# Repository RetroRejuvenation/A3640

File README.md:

# a3640
Somewhere for the A3640 project to live

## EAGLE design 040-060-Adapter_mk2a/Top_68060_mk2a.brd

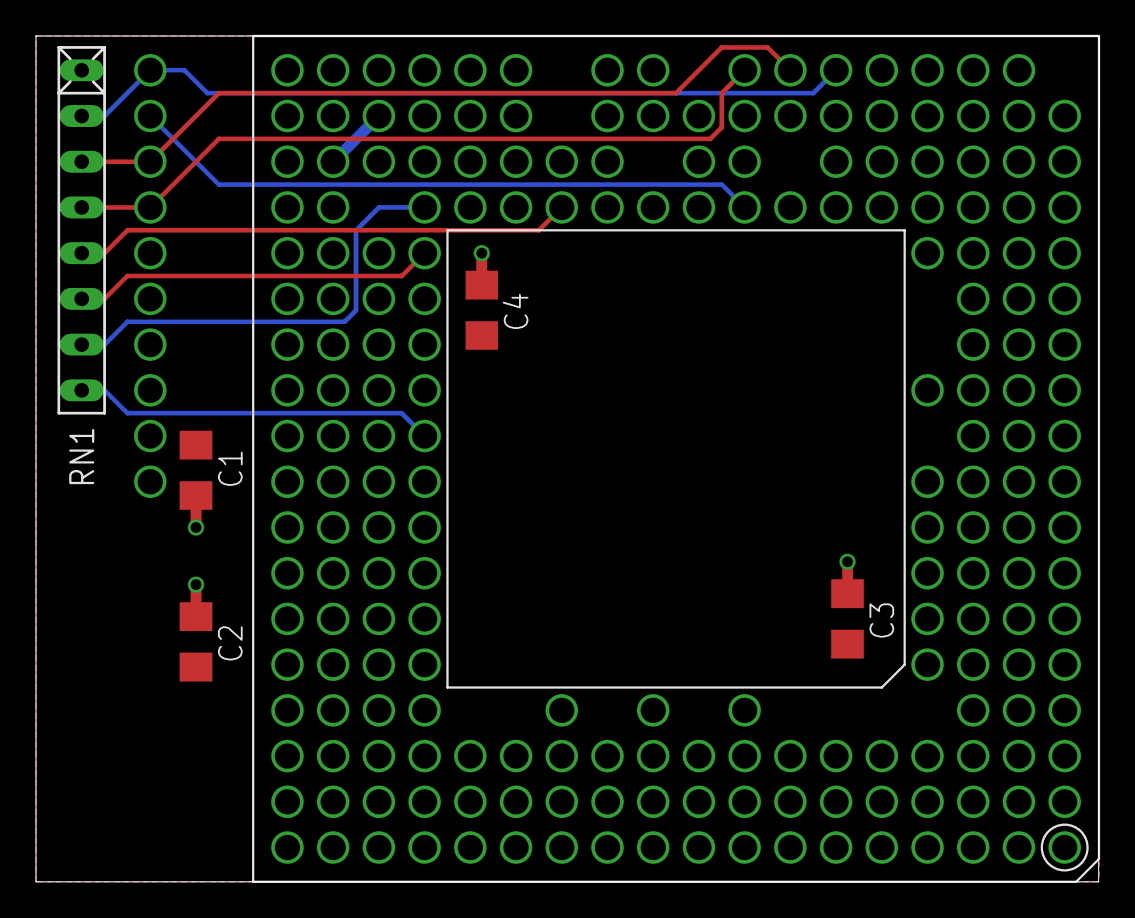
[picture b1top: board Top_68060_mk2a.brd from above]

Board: 2 copper layers, 59.1 x 47.0 mm, 7 parts (0 on the bottom side), 10 nets.

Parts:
C1, C2, C3, C4: 100n; C1206
IC1: MC68060RCPGA_BIG; PGA206_BIG
RN1: 4k7; RN-8
U$1: 10POL; 10-PIN-1.4HOLES

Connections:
+3V3: C1.1, C2.1, C3.1, C4.1, IC1.B05, IC1.B09, IC1.B14, IC1.C02, IC1.C05, IC1.C08, IC1.C10, IC1.C12, IC1.C14, IC1.C17, IC1.D08, IC1.D10, IC1.D12, IC1.D15, IC1.E04, IC1.E15, IC1.G02, IC1.G04, IC1.G15, IC1.G17, IC1.H03, IC1.H16, IC1.J03, IC1.J04, IC1.J15, IC1.J16, IC1.L04, IC1.L16, IC1.M02, IC1.M03, IC1.M17, IC1.N15, IC1.P04, IC1.Q10, IC1.R02, IC1.R05, IC1.R08, IC1.R12, IC1.R17, IC1.S08, IC1.S16, RN1.1, U$1.P$5, U$1.P$6, U$1.P$7, U$1.P$8, U$1.P$9, U$1.P$10
BTT: IC1.Q15, RN1.7
CLA: IC1.K15, RN1.8
CLKEN: IC1.Q08, U$1.P$2
GND: C1.2, C2.2, C3.2, C4.2, IC1.B02, IC1.B04, IC1.B06, IC1.B08, IC1.B10, IC1.B13, IC1.B15, IC1.B17, IC1.C06, IC1.C07, IC1.C09, IC1.C11, IC1.C13, IC1.D02, IC1.D17, IC1.F02, IC1.F04, IC1.F15, IC1.F17, IC1.H02, IC1.H04, IC1.H15, IC1.H17, IC1.K03, IC1.K16, IC1.L02, IC1.L03, IC1.L17, IC1.M16, IC1.N02, IC1.N17, IC1.Q02, IC1.Q09, IC1.Q11, IC1.Q17, IC1.R04, IC1.R06, IC1.R11, IC1.R13, IC1.S02, IC1.S09, IC1.S10, IC1.S15, IC1.S17
IPL0: IC1.T08, RN1.4, U$1.P$4
IPL1: IC1.T07, RN1.3, U$1.P$3
IPL2: IC1.T06, RN1.2, U$1.P$1
SNOOP: IC1.P15, RN1.6
TRA: IC1.Q12, RN1.5

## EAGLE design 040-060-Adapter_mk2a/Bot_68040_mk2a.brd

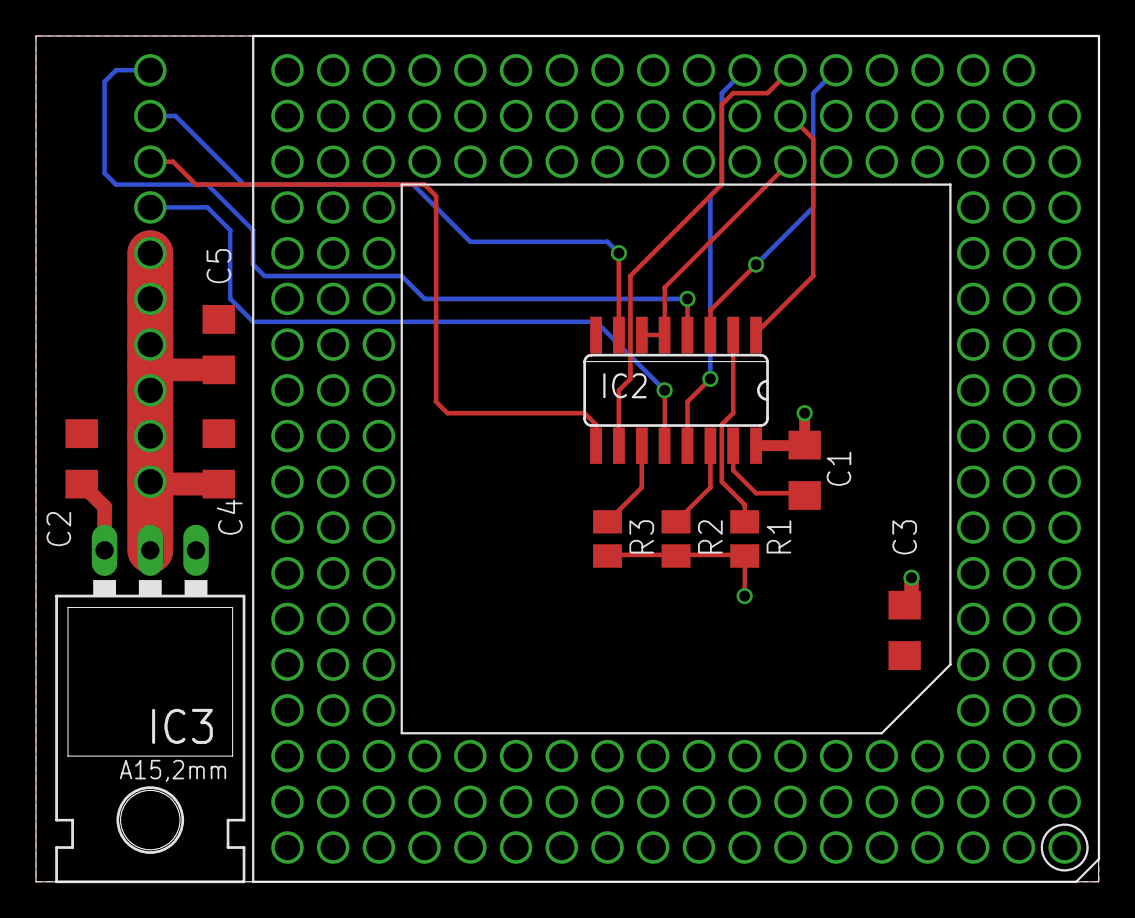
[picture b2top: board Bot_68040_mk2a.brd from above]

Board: 2 copper layers, 59.1 x 47.0 mm, 12 parts (0 on the bottom side), 15 nets.

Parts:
C1, C2, C4: 100n; C1206
C3, C5: 10u; C1206
IC1: PGA179_BIG
IC2: 74F257; SO16
IC3: LT1084; 317TL
R1, R2, R3: 4k7; M0805
U$1: 10POL; 10-PIN-1.4HOLES

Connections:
40_BCLK: IC1.R07, IC2.5, IC2.6
40_IPL0: IC1.T08, IC2.13
40_IPL1: IC1.T07, IC2.10
40_IPL2: IC1.T06, IC2.3
40_RSTI: IC1.S07, IC2.1
60_CLKEN: IC2.7, U$1.P$2
60_IPL0: IC2.12, U$1.P$4
60_IPL1: IC2.9, U$1.P$3
60_IPL2: IC2.4, U$1.P$1
+3V3: C4.1, C5.1, IC3.2, U$1.P$5, U$1.P$6, U$1.P$7, U$1.P$8, U$1.P$9, U$1.P$10
GND: C1.2, C2.2, C3.2, C4.2, C5.2, IC1.B02, IC1.B04, IC1.B06, IC1.B08, IC1.B10, IC1.B13, IC1.B15, IC1.B17, IC1.C06, IC1.C07, IC1.C09, IC1.C11, IC1.C13, IC1.D02, IC1.D17, IC1.F02, IC1.F17, IC1.H02, IC1.H17, IC1.K03, IC1.K16, IC1.L02, IC1.L03, IC1.L17, IC1.M16, IC1.N02, IC1.N17, IC1.Q02, IC1.Q17, IC1.R04, IC1.R06, IC1.R10, IC1.R11, IC1.R13, IC1.S02, IC1.S09, IC1.S10, IC1.S15, IC1.S17, IC1.T04, IC2.8, IC2.15, IC3.1
unnamed: IC2.2, R1.1
unnamed: IC2.11, R3.1
unnamed: IC2.14, R2.1
VCC: C1.1, C2.1, C3.1, IC1.B05, IC1.B09, IC1.B14, IC1.C02, IC1.C05, IC1.C08, IC1.C10, IC1.C12, IC1.C14, IC1.C17, IC1.G02, IC1.G17, IC1.H03, IC1.H16, IC1.J03, IC1.J16, IC1.L16, IC1.M02, IC1.M03, IC1.M17, IC1.R02, IC1.R05, IC1.R08, IC1.R12, IC1.R17, IC1.S08, IC1.S16, IC2.16, IC3.3, R1.2, R2.2, R3.2

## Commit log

2017-04-06 Initial commit
    Initial commit based on what I had available from the defunct
    TerribleFire repo.
2017-04-06 Misc files.
    Found a few more A3640 bits which might be useful.
2017-04-06 ignore DS_Store files.
